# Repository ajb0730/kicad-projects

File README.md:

# kicad-projects
Repo to track various KiCad projects

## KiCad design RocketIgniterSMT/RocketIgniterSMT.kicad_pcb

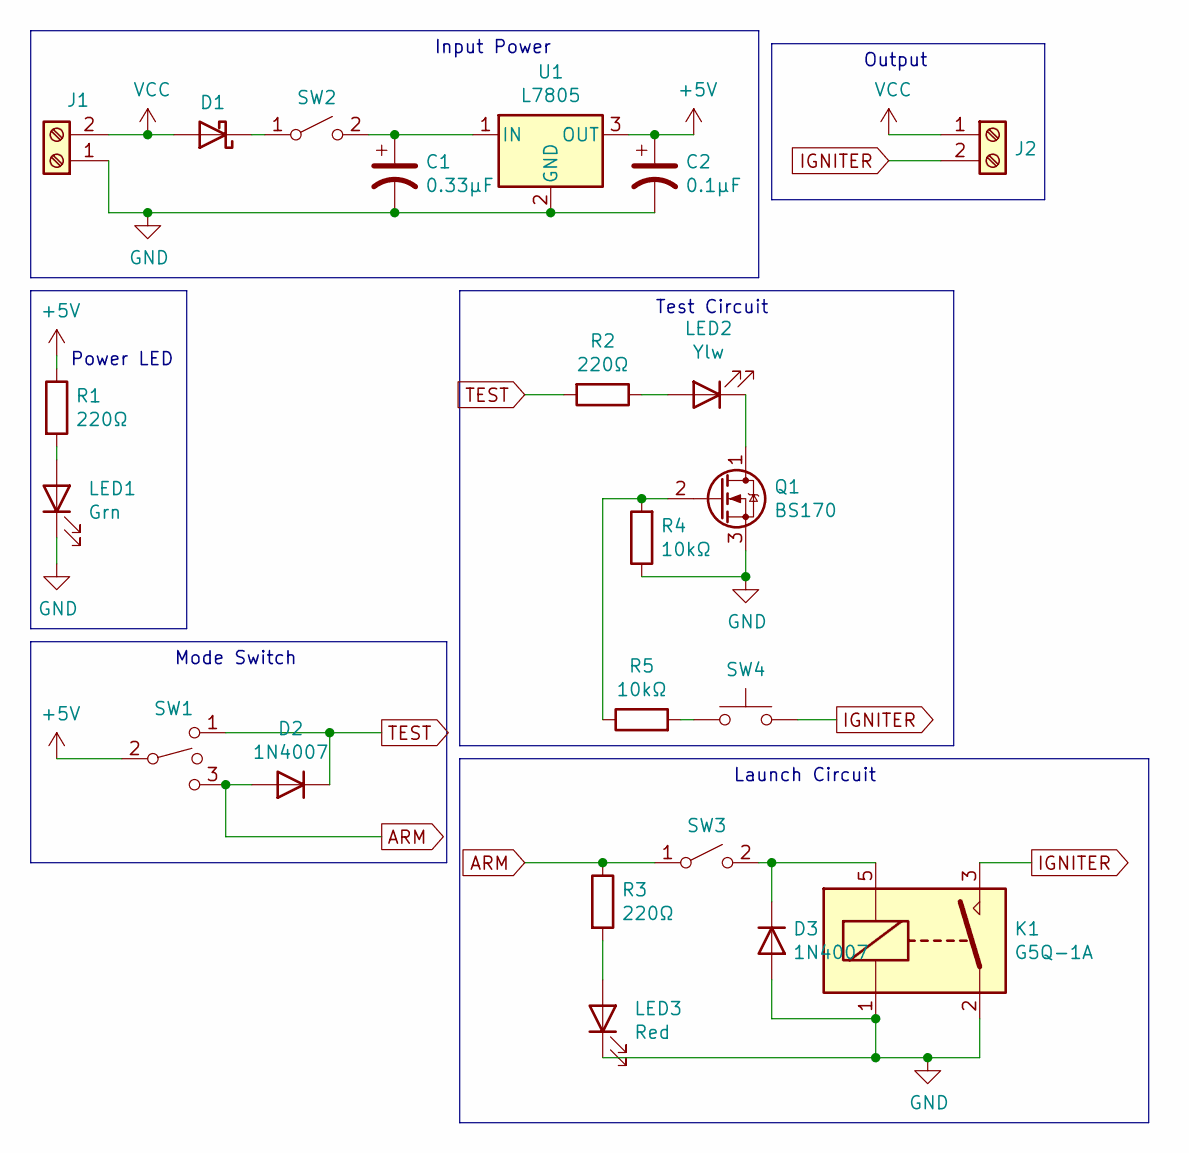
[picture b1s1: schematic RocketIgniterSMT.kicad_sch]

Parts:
C1: 0.33µF; CP_Radial_Tantal_D4.5mm_P2.50mm; MfrPartNo TAP334K035SCS
C2: 0.1µF; CP_Radial_Tantal_D4.5mm_P2.50mm; MfrPartNo TAP104M050SCS
D1: D_Schottky; D_DO-41_SOD81_P10.16mm_Horizontal; MfrPartNo SB140
D2, D3: 1N4007; D_DO-41_SOD81_P10.16mm_Horizontal; MfrPartNo 1N4007T-G
J1, J2: Screw_Terminal_01x02; TerminalBlock_TE_282834-2_1x02_P2.54mm_Horizontal; MfrPartNo 282834-2
K1: G5Q-1A; Relay_SPST_Omron-G5Q-1A; MfrPartNo G5Q-1A4-EU DC5
LED1: Grn; SolderWire-1sqmm_1x02_P7.8mm_D1.4mm_OD3.9mm
LED2: Ylw; SolderWire-1sqmm_1x02_P7.8mm_D1.4mm_OD3.9mm
LED3: Red; SolderWire-1sqmm_1x02_P7.8mm_D1.4mm_OD3.9mm
Q1: BS170; TO-92_Inline_Wide; MfrPartNo BS170
R1, R2, R3: 220Ω; R_Axial_DIN0207_L6.3mm_D2.5mm_P10.16mm_Horizontal
R4, R5: 10kΩ; R_Axial_DIN0207_L6.3mm_D2.5mm_P10.16mm_Horizontal
SW1: SW_SPDT_MSM; SolderWire-1sqmm_1x03_P7.8mm_D1.4mm_OD3.9mm
SW2, SW3: SW_SPST; SolderWire-1sqmm_1x02_P7.8mm_D1.4mm_OD3.9mm
SW4: SW_Push; SolderWire-1sqmm_1x02_P7.8mm_D1.4mm_OD3.9mm
U1: L7805; TO-220-3_Vertical; MfrPartNo MC7805BTG

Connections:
+5V: C2.1, R1.1, SW1.2, U1.3 (OUT)
ARM: D2.2 (A), R3.1, SW1.3, SW3.1 (A)
GND: C1.2, C2.2, D3.2 (A), J1.1, K1.1, K1.2, LED1.1 (K), LED3.1 (K), Q1.3 (S), R4.1, U1.2 (GND)
IGNITER: J2.2, K1.3, SW4.2
unnamed: C1.1, SW2.2 (B), U1.1 (IN)
unnamed: D1.1 (K), SW2.1 (A)
unnamed: D3.1 (K), K1.5, SW3.2 (B)
unnamed: LED1.2 (A), R1.2
unnamed: LED2.1 (K), Q1.1 (D)
unnamed: LED2.2 (A), R2.1
unnamed: LED3.2 (A), R3.2
unnamed: Q1.2 (G), R4.2, R5.1
unnamed: R5.2, SW4.1
TEST: D2.1 (K), R2.2, SW1.1
VCC: D1.2 (A), J1.2, J2.1

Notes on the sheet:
Input Power
Launch Circuit
Output
Mode Switch
Test Circuit
Power LED

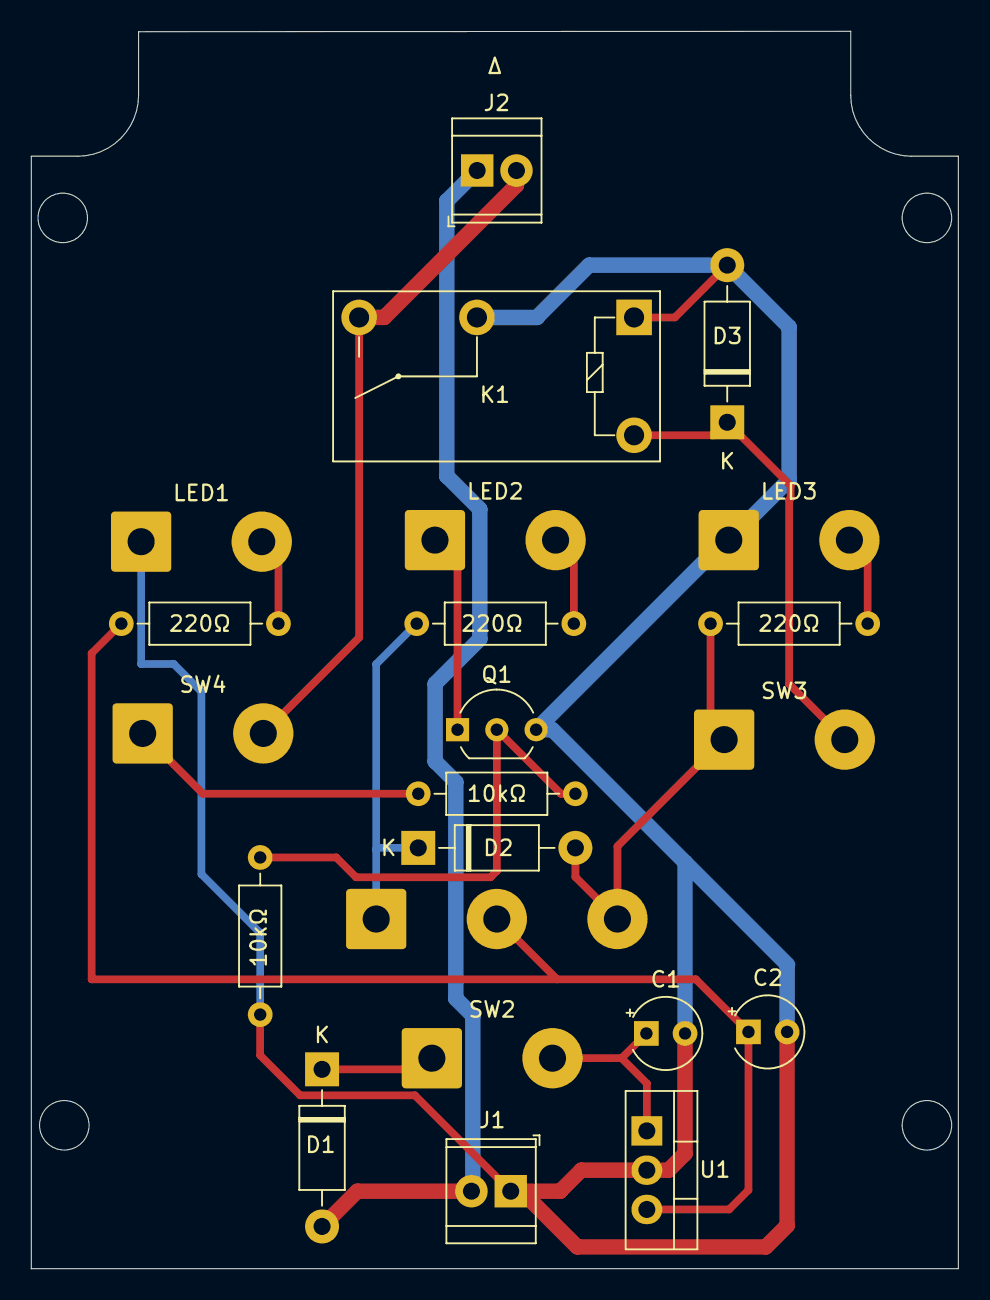
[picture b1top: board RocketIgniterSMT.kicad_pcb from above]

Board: 2 copper layers, 59.9 x 80.0 mm, 22 parts (0 on the bottom side), 15 nets.

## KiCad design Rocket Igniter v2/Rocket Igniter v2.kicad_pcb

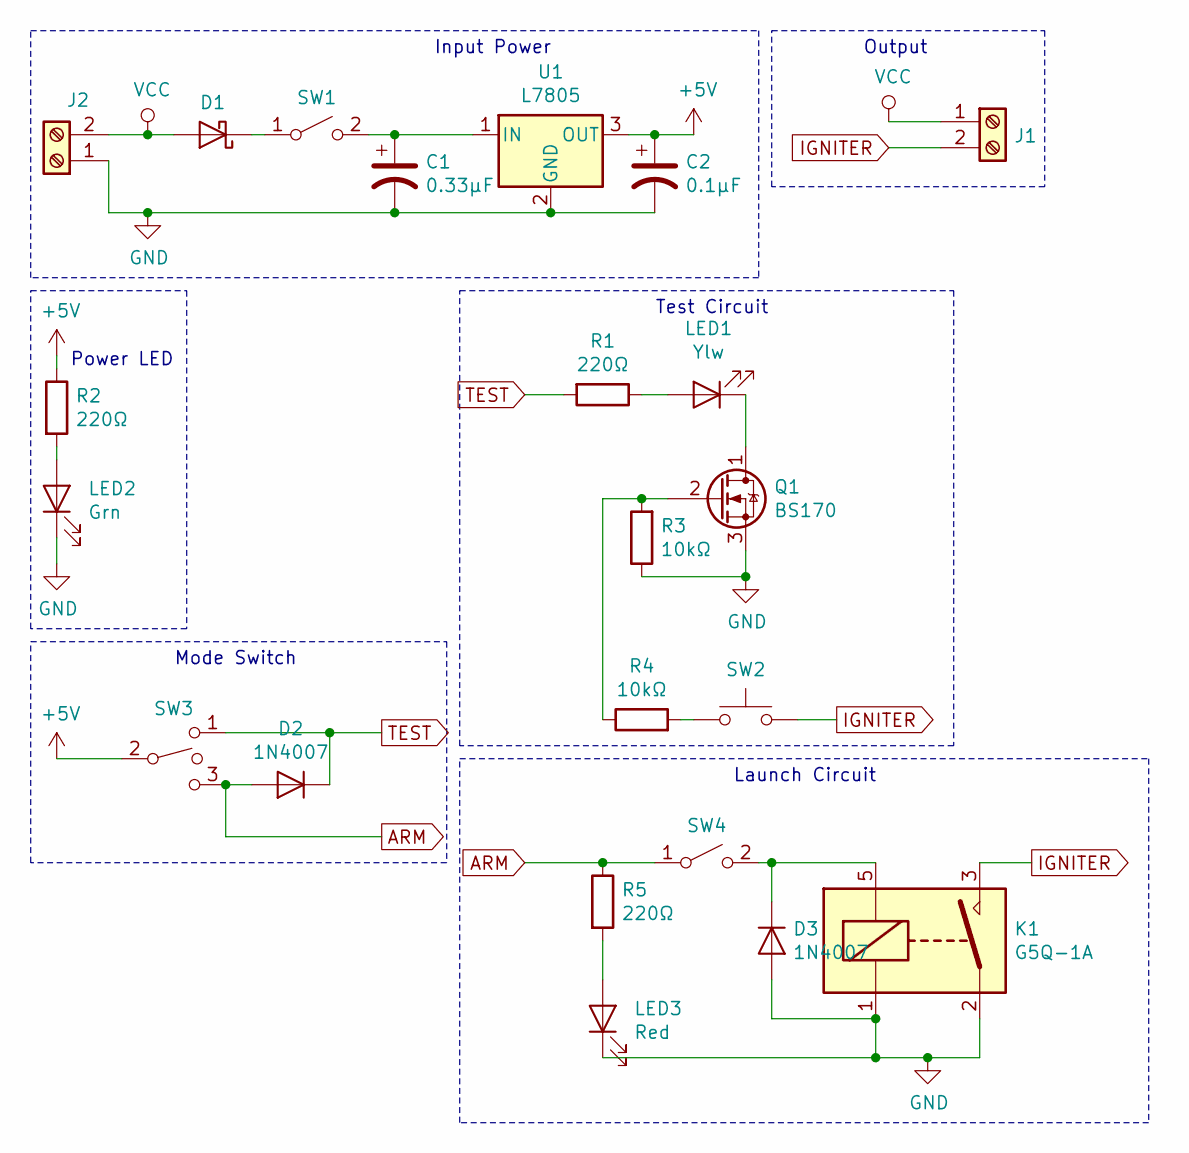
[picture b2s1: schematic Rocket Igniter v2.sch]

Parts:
C1: 0.33µF; C_0201_0603Metric
C2: 0.1µF; C_0201_0603Metric
D1: D_Schottky; C_0201_0603Metric
D2, D3: 1N4007; C_0201_0603Metric
J1, J2: Screw_Terminal_01x02; TerminalBlock_TE_282834-2_1x02_P2.54mm_Horizontal
K1: G5Q-1A; Relay_SPST_Omron-G5Q-1A
LED1: Ylw; SolderWirePad_1x02_P7.62mm_Drill2.5mm
LED2: Grn; SolderWirePad_1x02_P7.62mm_Drill2.5mm
LED3: Red; SolderWirePad_1x02_P7.62mm_Drill2.5mm
Q1: BS170; SOT-23
R1, R2, R5: 220Ω; R_0603_1608Metric
R3, R4: 10kΩ; R_0603_1608Metric
SW1, SW4: SW_SPST; SolderWirePad_1x02_P7.62mm_Drill2.5mm
SW2: SW_Push; SolderWirePad_1x02_P7.62mm_Drill2.5mm
SW3: SW_SPDT_MSM; SolderWirePad_1x03_P7.62mm_Drill2.5mm
U1: L7805; SOT-23

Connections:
+5V: C2.1, R2.1, SW3.2, U1.3 (OUT)
ARM: D2.2 (A), R5.1, SW3.3, SW4.1 (A)
GND: C1.2, C2.2, D3.2 (A), J2.1, K1.1, K1.2, LED2.1 (K), LED3.1 (K), Q1.3 (S), R3.1, U1.2 (GND)
IGNITER: J1.2, K1.3, SW2.2
unnamed: C1.1, SW1.2 (B), U1.1 (IN)
unnamed: D1.1 (K), SW1.1 (A)
unnamed: D3.1 (K), K1.5, SW4.2 (B)
unnamed: LED1.1 (K), Q1.1 (D)
unnamed: LED1.2 (A), R1.1
unnamed: LED2.2 (A), R2.2
unnamed: LED3.2 (A), R5.2
unnamed: Q1.2 (G), R3.2, R4.1
unnamed: R4.2, SW2.1
TEST: D2.1 (K), R1.2, SW3.1
VCC: D1.2 (A), J1.1, J2.2

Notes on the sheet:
Power LED
Input Power
Mode Switch
Test Circuit
Launch Circuit
Output

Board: 2 copper layers, 22 parts (0 on the bottom side), 15 nets, no tracks yet.

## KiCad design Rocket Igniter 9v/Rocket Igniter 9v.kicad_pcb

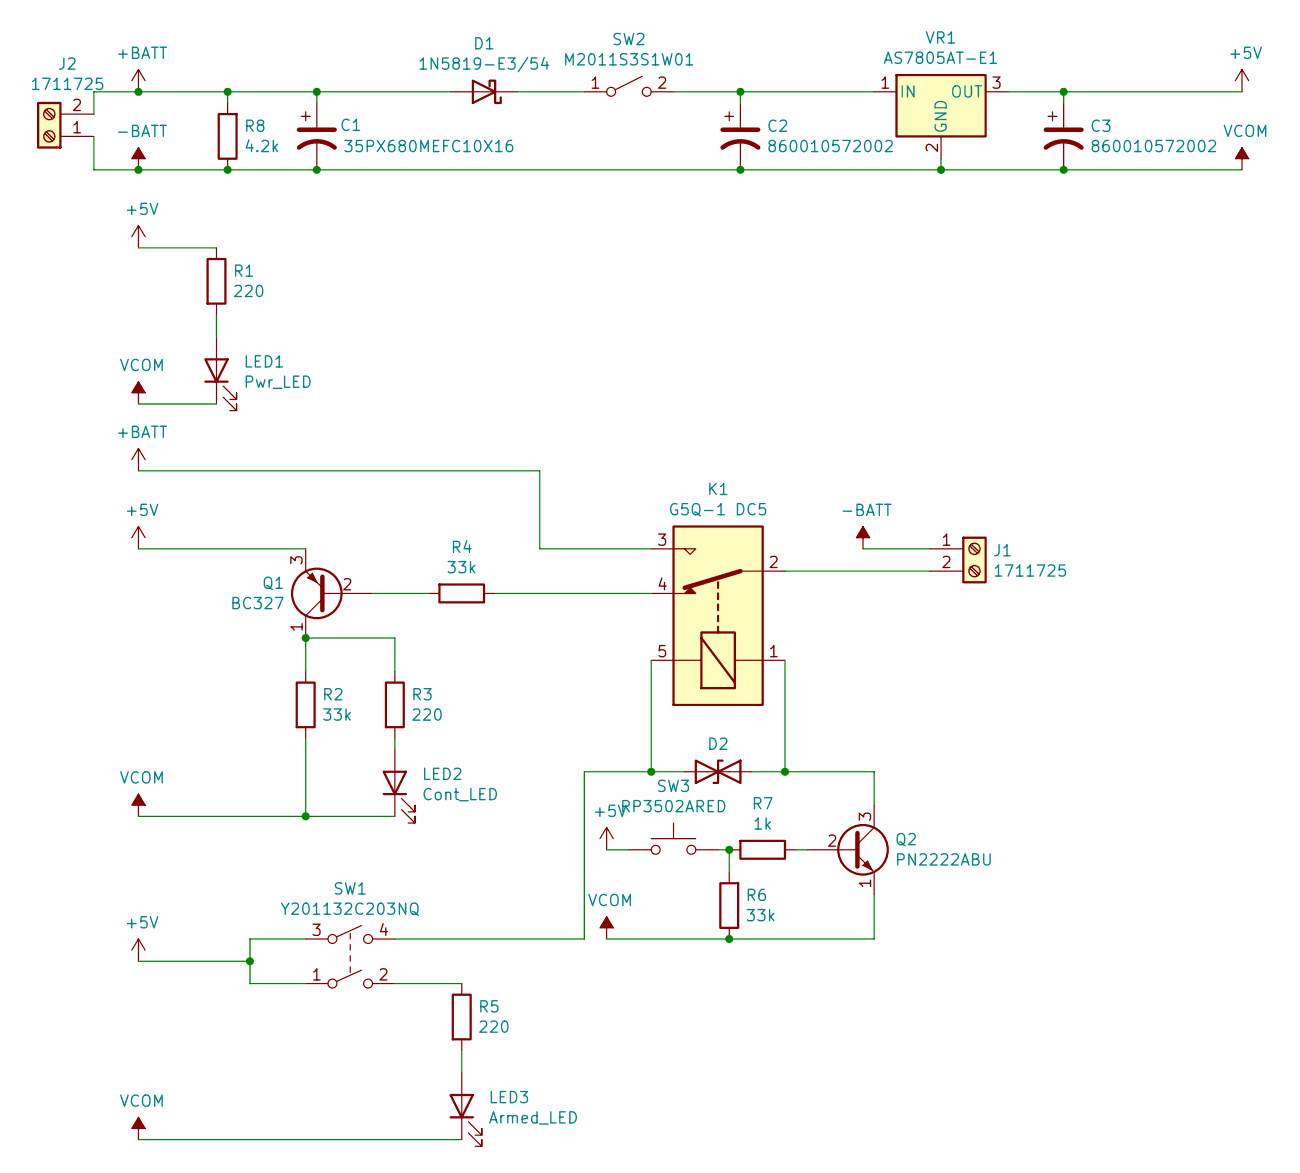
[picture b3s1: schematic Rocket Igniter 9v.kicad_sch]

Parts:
C1: 35PX680MEFC10X16; C_Radial_D10.0mm_H16.0mm_P5.00mm
C2, C3: 860010572002; C_Radial_D5.0mm_H11.0mm_P2.00mm
D1: 1N5819-E3/54; D_DO-41_SOD81_P10.16mm_Horizontal
D2: P6KE6.8CA; D_DO-15_P10.16mm_Horizontal
J1, J2: 1711725; TerminalBlock_Phoenix_MKDS-1,5-2-5.08_1x02_P5.08mm_Horizont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
K1: G5Q-1 DC5; Relay_SPDT_Omron-G5Q-1
LED1: Pwr_LED; LED_D5.0mm
LED2: Cont_LED; LED_D5.0mm
LED3: Armed_LED; LED_D5.0mm
Q1: BC327; TO-92_Inline
Q2: PN2222ABU; TO-92_Inline
R1, R3, R5: 220; R_Axial_DIN0207_L6.3mm_D2.5mm_P10.16mm_Horizontal
R2, R4, R6: 33k; R_Axial_DIN0207_L6.3mm_D2.5mm_P10.16mm_Horizontal
R7: 1k; R_Axial_DIN0207_L6.3mm_D2.5mm_P10.16mm_Horizontal
R8: 4.2k; R_Axial_DIN0207_L6.3mm_D2.5mm_P10.16mm_Horizontal
SW1: Y201132C203NQ; SolderWirePad_2x02_P5.08mm_Drill1.5mm
SW2: M2011S3S1W01; SolderWirePad_1x02_P3.81mm_Drill1.2mm
SW3: RP3502ARED; SolderWirePad_1x02_P5.08mm_Drill1.5mm
VR1: AS7805AT-E1; TO-220-3_Vertical

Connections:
+5V: C3.1, Q1.3 (E), R1.1, SW1.1, SW1.3, SW3.1, VR1.3 (OUT)
+BATT: C1.1, D1.2 (A), J2.2, K1.3, R8.2
-BATT: C1.2, C2.2, C3.2, J1.1, J2.1, LED1.1 (K), LED2.1 (K), LED3.1 (K), Q2.1 (E), R2.2, R6.1, R8.1, VR1.2 (GND)
unnamed: C2.1, SW2.2 (B), VR1.1 (IN)
unnamed: D1.1 (K), SW2.1 (A)
unnamed: D2.1 (A1), K1.5, SW1.4
unnamed: D2.2 (A2), K1.1, Q2.3 (C)
unnamed: J1.2, K1.2
unnamed: K1.4, R4.1
unnamed: LED1.2 (A), R1.2
unnamed: LED2.2 (A), R3.2
unnamed: LED3.2 (A), R5.2
unnamed: Q1.1 (C), R2.1, R3.1
unnamed: Q1.2 (B), R4.2
unnamed: Q2.2 (B), R7.1
unnamed: R5.1, SW1.2
unnamed: R6.2, R7.2, SW3.2

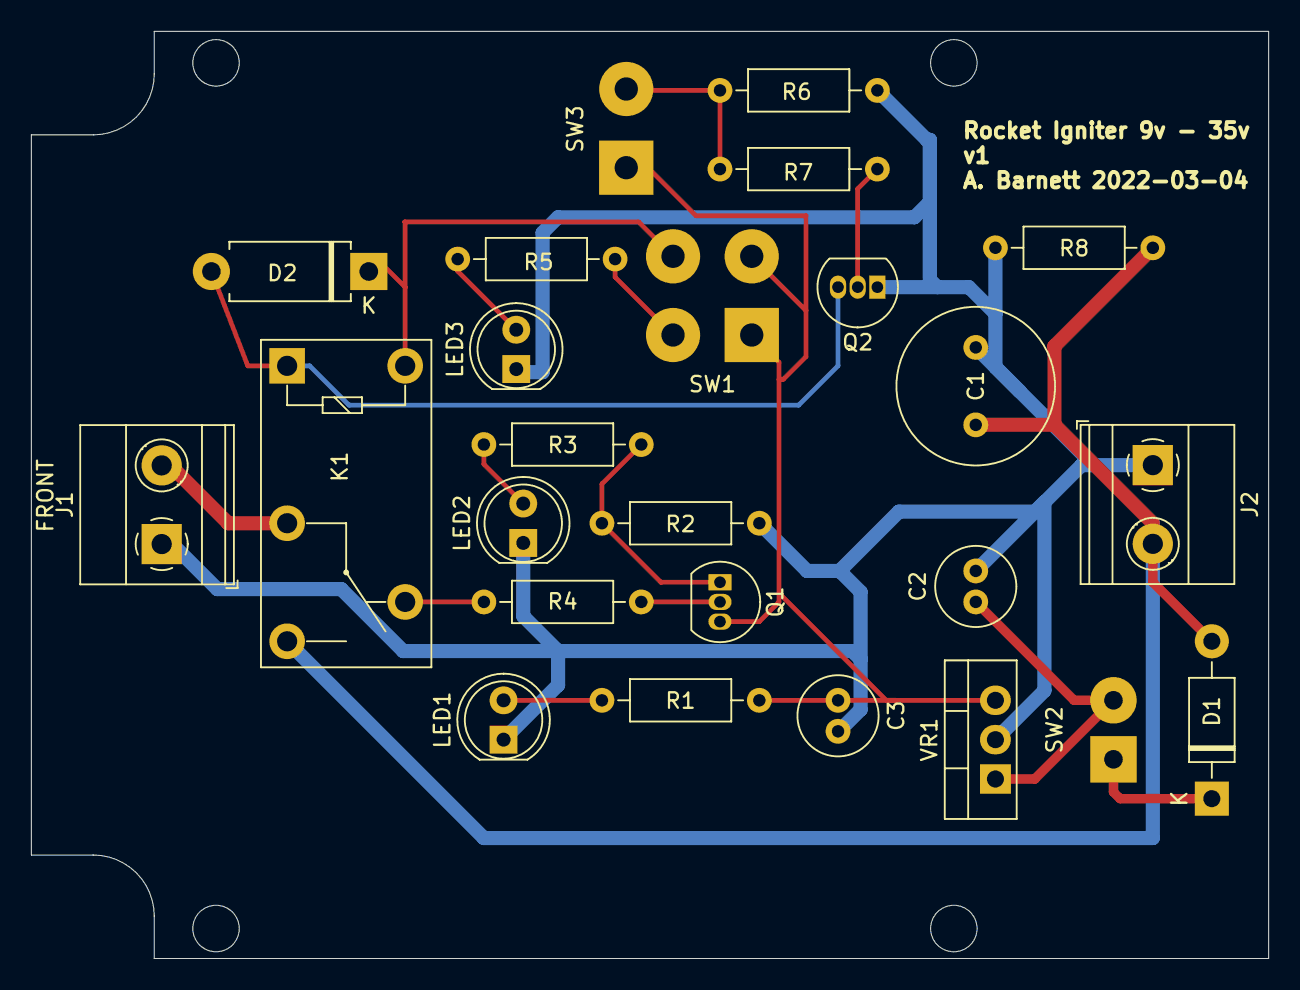
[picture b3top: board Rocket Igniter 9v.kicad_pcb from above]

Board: 2 copper layers, 79.9 x 59.8 mm, 26 parts (0 on the bottom side), 17 nets.

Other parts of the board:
locked: MountingHole_3mm

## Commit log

2022-03-04 init(9v): 9v Rocket Igniter
2022-03-05 tidied the pcb
2022-03-05 adjust silkscreen
2022-03-05 clean up schematic
2022-03-11 checkpoint
2022-03-15 add 2
2022-03-16 new version
